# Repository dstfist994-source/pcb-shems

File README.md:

# Industrial IoT Smart Edge Device & Isolated Energy Controller

**A robust, mixed-signal hardware platform designed for AC mains energy monitoring, power conversion, and isolated load control. Engineered with high-voltage clearance, discrete signal shifting, and inductive load protection.**

---

## 📖 Overview

This **Smart Edge Node** is an industrial/home energy monitoring and switching board that bridges high-voltage AC mains power with low-voltage microcontroller logic. Designed with a focus on **analog hardware reliability**, **power distribution**, and **galvanic isolation**, the design integrates on-board AC-DC regulated conversion, discrete MOSFET level translation, and an optoisolated transistor relay driver with flyback suppression.

The system utilizes an **ESP8266 (Lolin)** for edge processing and software-driven UART communication with a **PZEM-004T** metering module, enabling real-time telemetry publication over Wi-Fi (MQTT/HTTP) while safely controlling heavy AC electrical loads.

---

## 📸 Visuals

| **3D PCB Render** | **PCB Layout & Routing** | **Hardware Schematic** |
|:---:|:---:|:---:|
|  |  |  |
| *KiCad 3D Ray-traced Board View* | *2-Layer Trace & High-Voltage Clearance* | *System Schematic Architecture* |

---

## ⚡ Hardware & Analog Engineering Highlights

### 1. Power Management & Bulk Decoupling
* **Integrated AC-DC Conversion:** Employs an on-board **Hi-Link HLK-5M05** module to convert $230\text{V AC}$ mains input directly down to a regulated $5\text{V DC}$ supply rail.
* **Transient Suppression & Ripple Filtering:** Features a high-capacity **$470\ \mu\text{F}$ bulk electrolytic capacitor ($C1$)** across the $5\text{V}$ rail to absorb voltage dips, suppress power supply ripple, and maintain rail stability during high instantaneous relay coil pull-in current.

### 2. Level Translation & Signal Integrity
* **Bi-Directional MOSFET Level Shifting:** Incorporates a discrete **BSS138 N-channel MOSFET Logic Level Converter ($U4$)** to bridge the $3.3\text{V CMOS}$ GPIO output of the ESP8266 ($D1$) to the $5\text{V TTL}$ driver logic without overdriving MCU input pins.
* **Isolated UART Interface:** Software Serial UART interface ($D6/D7$) connecting to the **PZEM-004T** energy metering frontend for accurate RMS Voltage, Current, Active Power, Frequency, and Power Factor acquisition.

### 3. Optoisolated Load Control & Inductive Suppression
* **Galvanic Isolation Drive Stage:** High-voltage AC switching is completely isolated from low-voltage digital control using a **PC817 Optocoupler** and an **S8050 NPN transistor** driver stage.
* **Back-EMF Inductive Protection:** A **1N4007 flyback suppression diode ($D1$)** is placed across the **SLA-05VDC** relay coil to clamp high-voltage inductive spikes generated during coil de-energization, protecting switching silicon from overshoot breakdown.
* **Visual Diagnostics:** Integrated LED indicator with current-limiting resistor ($1\text{ k}\Omega$) for visual relay status feedback.

### 4. High-Voltage PCB Layout & Safety Design
* **Creepage & Clearance:** Wide physical clearance and routing separation between the $230\text{V}$ AC mains region (Live/Neutral) and low-voltage $5\text{V}/3.3\text{V}$ DC signal planes to prevent electrical arcing.
* **Current-Handling Traces:** Heavy trace widths utilized on AC Live/Neutral routing and high-current relay switching paths to minimize trace impedance, drop, and thermal rise under heavy electrical load.

---

## 🛠 Subsystem Breakdown

| Subsystem | Circuitry / Components | Function |
| :--- | :--- | :--- |
| **Power Supply** | HLK-5M05 + $470\ \mu\text{F}$ Capacitor | AC-DC Step-down ($230\text{V AC} \to 5\text{V DC}$) & Rail Filtering |
| **Microcontroller** | ESP8266 (Lolin V3 Footprint) | Wireless Telemetry, MQTT, SoftSerial UART, GPIO Control |
| **Logic Level Conversion** | BSS138 MOSFET Level Shifter ($U4$) | $3.3\text{V} \leftrightarrow 5\text{V}$ Logic Level Translation |
| **Relay Driver** | PC817 Optocoupler + S8050 NPN + 1N4007 Diode | Isolated coil energization & Back-EMF suppression |
| **AC Load Control** | SLA-05VDC High-Power Relay | Heavy AC Load ON/OFF Disconnect |
| **Energy Measurement** | PZEM-004T AC Sensor | High-accuracy RMS Voltage, Current, & Power Telemetry |

---

## 👨‍💻 Authors

- **Suvam Seth**
  *Power Engineering Student | PCB Design | Analog Electronics & Systems Design*

- **Sarin Sanyal**
  *Power Engineering Student | Analog & Mixed-Signal Circuit Design | Embedded Hardware | AI*

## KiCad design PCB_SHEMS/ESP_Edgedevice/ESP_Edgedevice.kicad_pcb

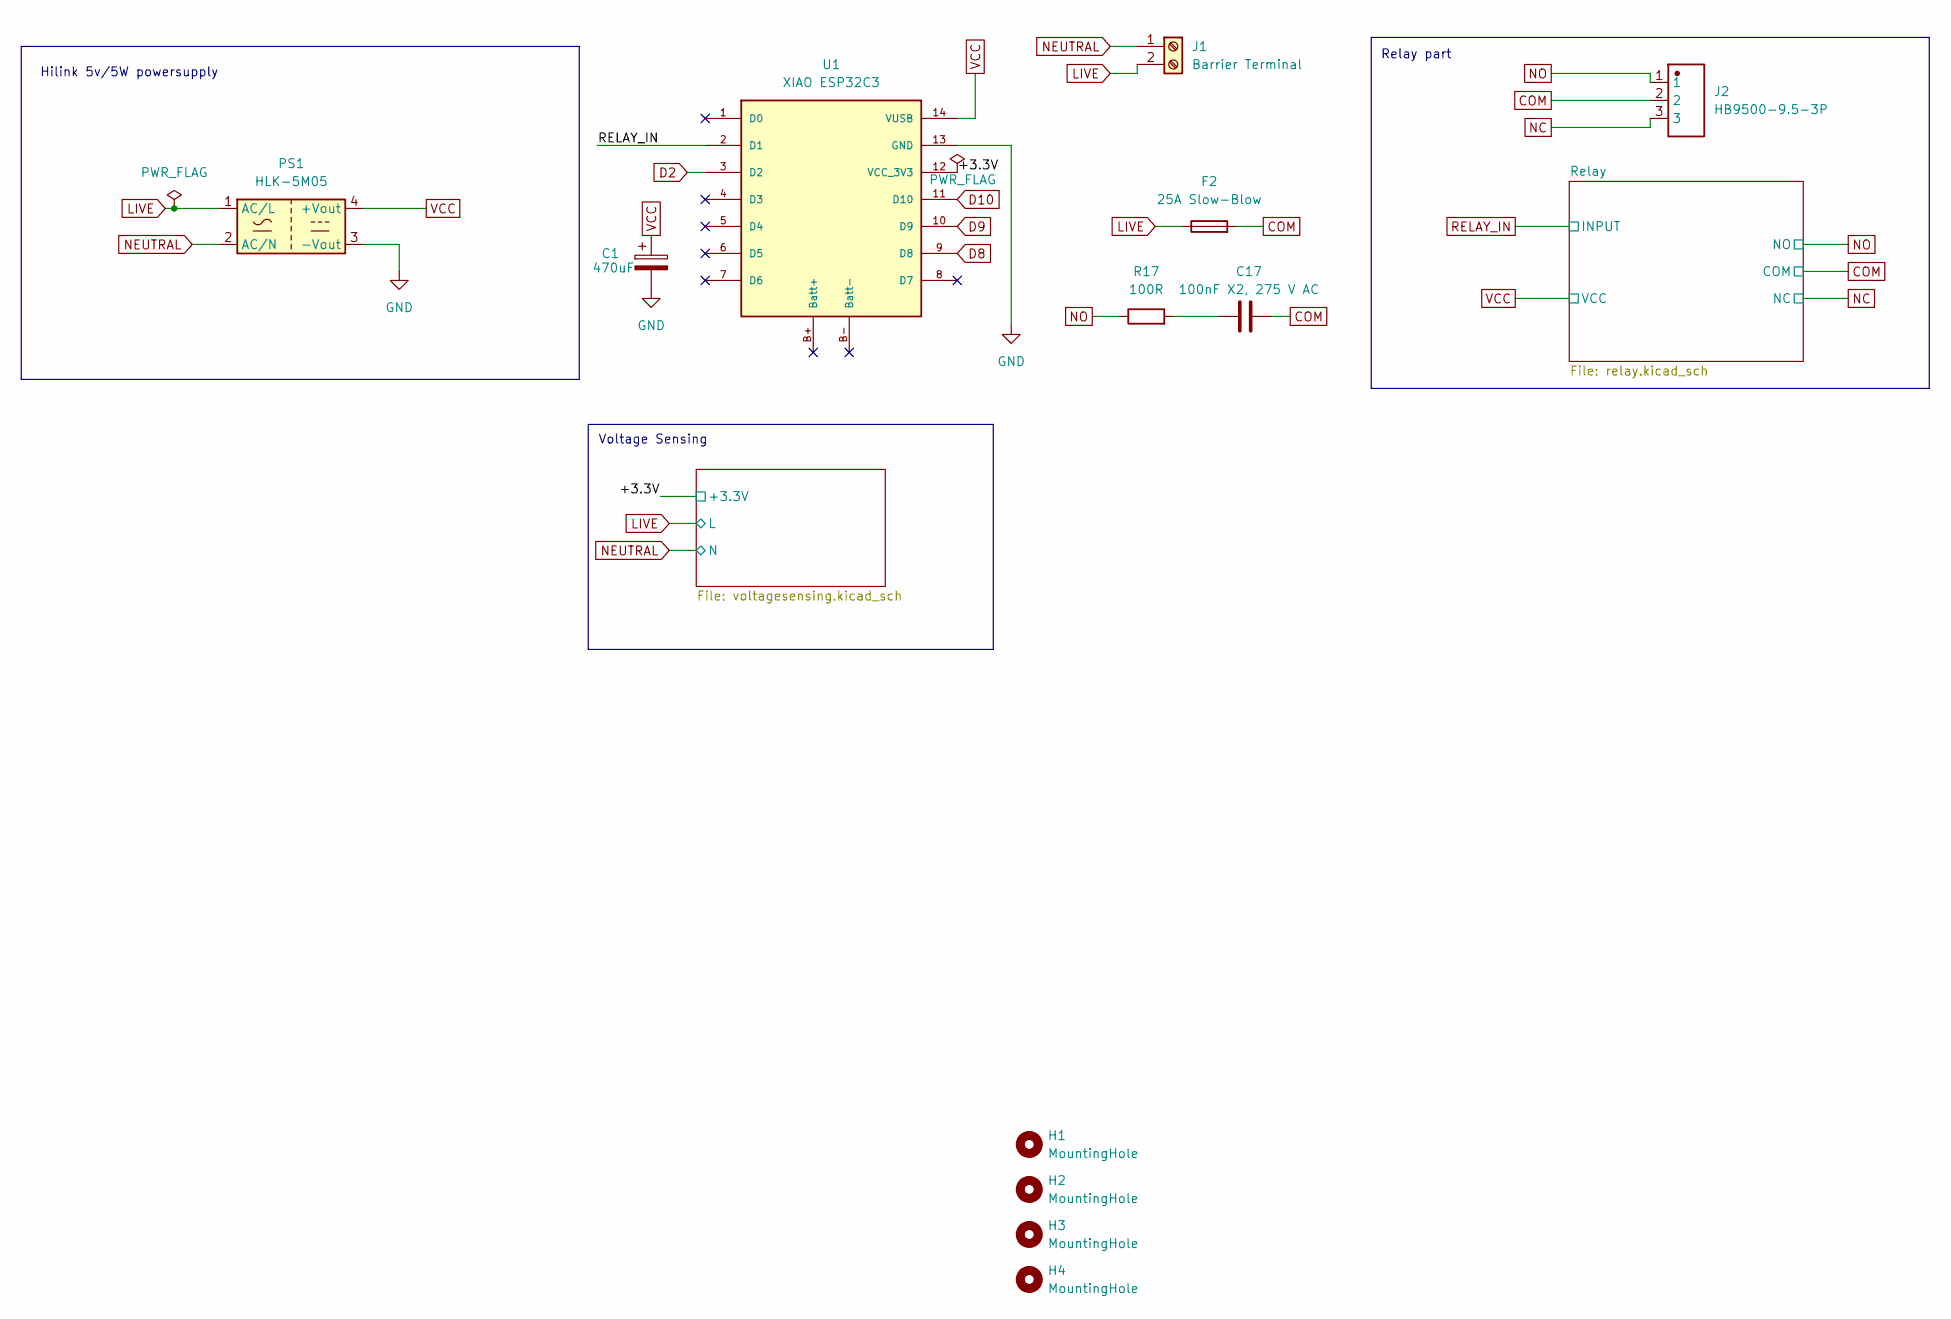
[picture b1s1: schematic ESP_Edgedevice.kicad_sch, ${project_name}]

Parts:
C1: 470uF; CP_Radial_D6.3mm_P2.50mm
C17: 100nF X2, 275 V AC; C_Rect_L18.0mm_W5.0mm_P15.00mm_FKS3_FKP3
F2: 25A Slow-Blow; Fuseholder_Cylinder-6.3x32mm_Schurter_0031-8002_Horizontal_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
H1, H2, H3, H4: MountingHole; MountingHole_2.1mm
J1: Barrier Terminal; PhoenixContact_MSTBA_2,5_2-G_1x02_P5.00mm_Horizontal
J2: HB9500-9.5-3P; HB9500_9.5-3P; Manufacturer Part HB9500-9.5-3P
PS1: HLK-5M05; Converter_ACDC_Hi-Link_HLK-5Mxx
R17: 100R; R_Axial_DIN0309_L9.0mm_D3.2mm_P12.70mm_Horizontal
U1: XIAO ESP32C3; XIAO_Socket_W15.24

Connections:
/+3.3V: U1.12 (VCC_3V3); also elsewhere on the board
COM: C17.2, F2.2, J2.2; also elsewhere on the board
D2: U1.3 (D2); also elsewhere on the board
D8: U1.9 (D8); also elsewhere on the board
D9: U1.10 (D9); also elsewhere on the board
D10: U1.11 (D10); also elsewhere on the board
GND: C1.2, PS1.3 (-Vout), U1.13 (GND); also elsewhere on the board
LIVE: F2.1, J1.2, PS1.1 (AC/L); also elsewhere on the board
NC: J2.3; also elsewhere on the board
NEUTRAL: J1.1, PS1.2 (AC/N); also elsewhere on the board
NO: J2.1, R17.1; also elsewhere on the board
unnamed: C17.1, R17.2
RELAY_IN: U1.2 (D1); also elsewhere on the board
VCC: C1.1, PS1.4 (+Vout), U1.14 (VUSB); also elsewhere on the board

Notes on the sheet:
Voltage Sensing
Relay part
Hilink 5v/5W powersupply

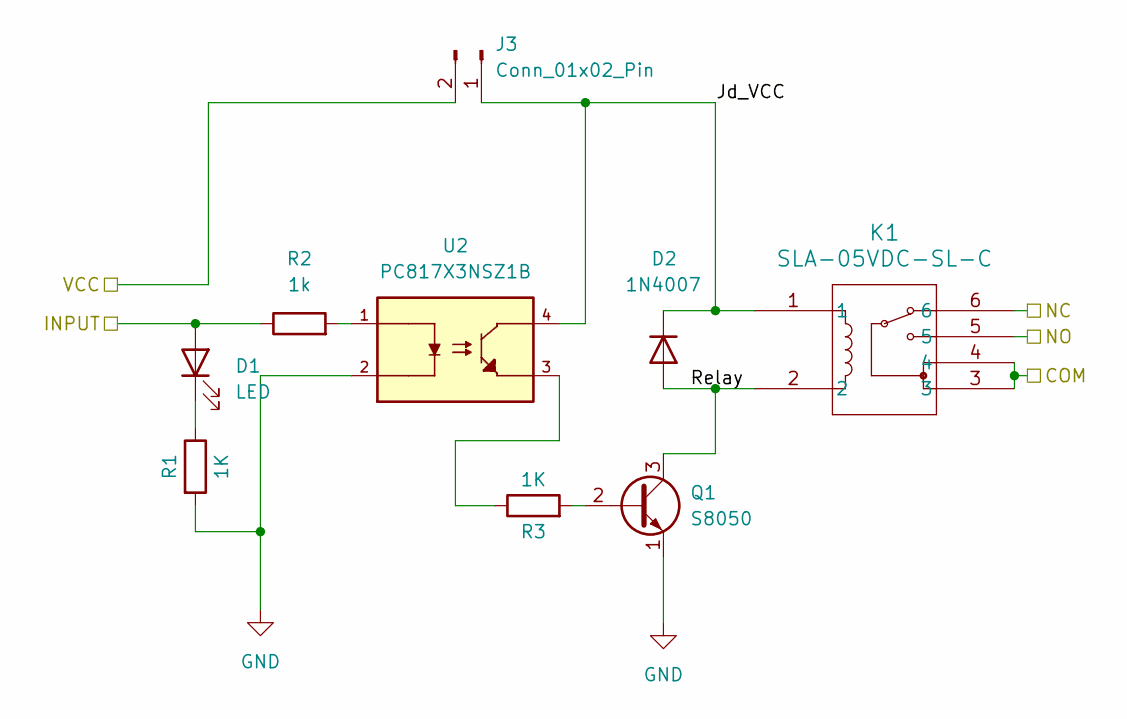
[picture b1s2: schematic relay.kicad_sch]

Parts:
D1: LED; LED_D3.0mm
D2: 1N4007; D_DO-41_SOD81_P10.16mm_Horizontal
J3: Conn_01x02_Pin; PinHeader_1x02_P2.54mm_Vertical
K1: SLA-05VDC-SL-C; RELAY-TH_SLA-XXVDC-XX-C
Q1: S8050; TO-92_Inline_Wide
R1, R3: 1K; R_1206_3216Metric
R2: 1k; R_1206_3216Metric
U2: PC817X3NSZ1B; DIP-4_W7.62mm; PARTREV October 7, 2016

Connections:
/Relay/Jd_VCC: D2.1 (K), J3.1, K1.1, U2.4
/Relay/Relay: D2.2 (A), K1.2, Q1.3 (C)
COM: K1.3, K1.4; also elsewhere on the board
GND: Q1.1 (E), R1.2, U2.2; also elsewhere on the board
NC: K1.6; also elsewhere on the board
NO: K1.5; also elsewhere on the board
unnamed: D1.1 (K), R1.1
unnamed: Q1.2 (B), R3.2
unnamed: R2.2, U2.1
unnamed: R3.1, U2.3
RELAY_IN: D1.2 (A), R2.1; also elsewhere on the board
VCC: J3.2; also elsewhere on the board

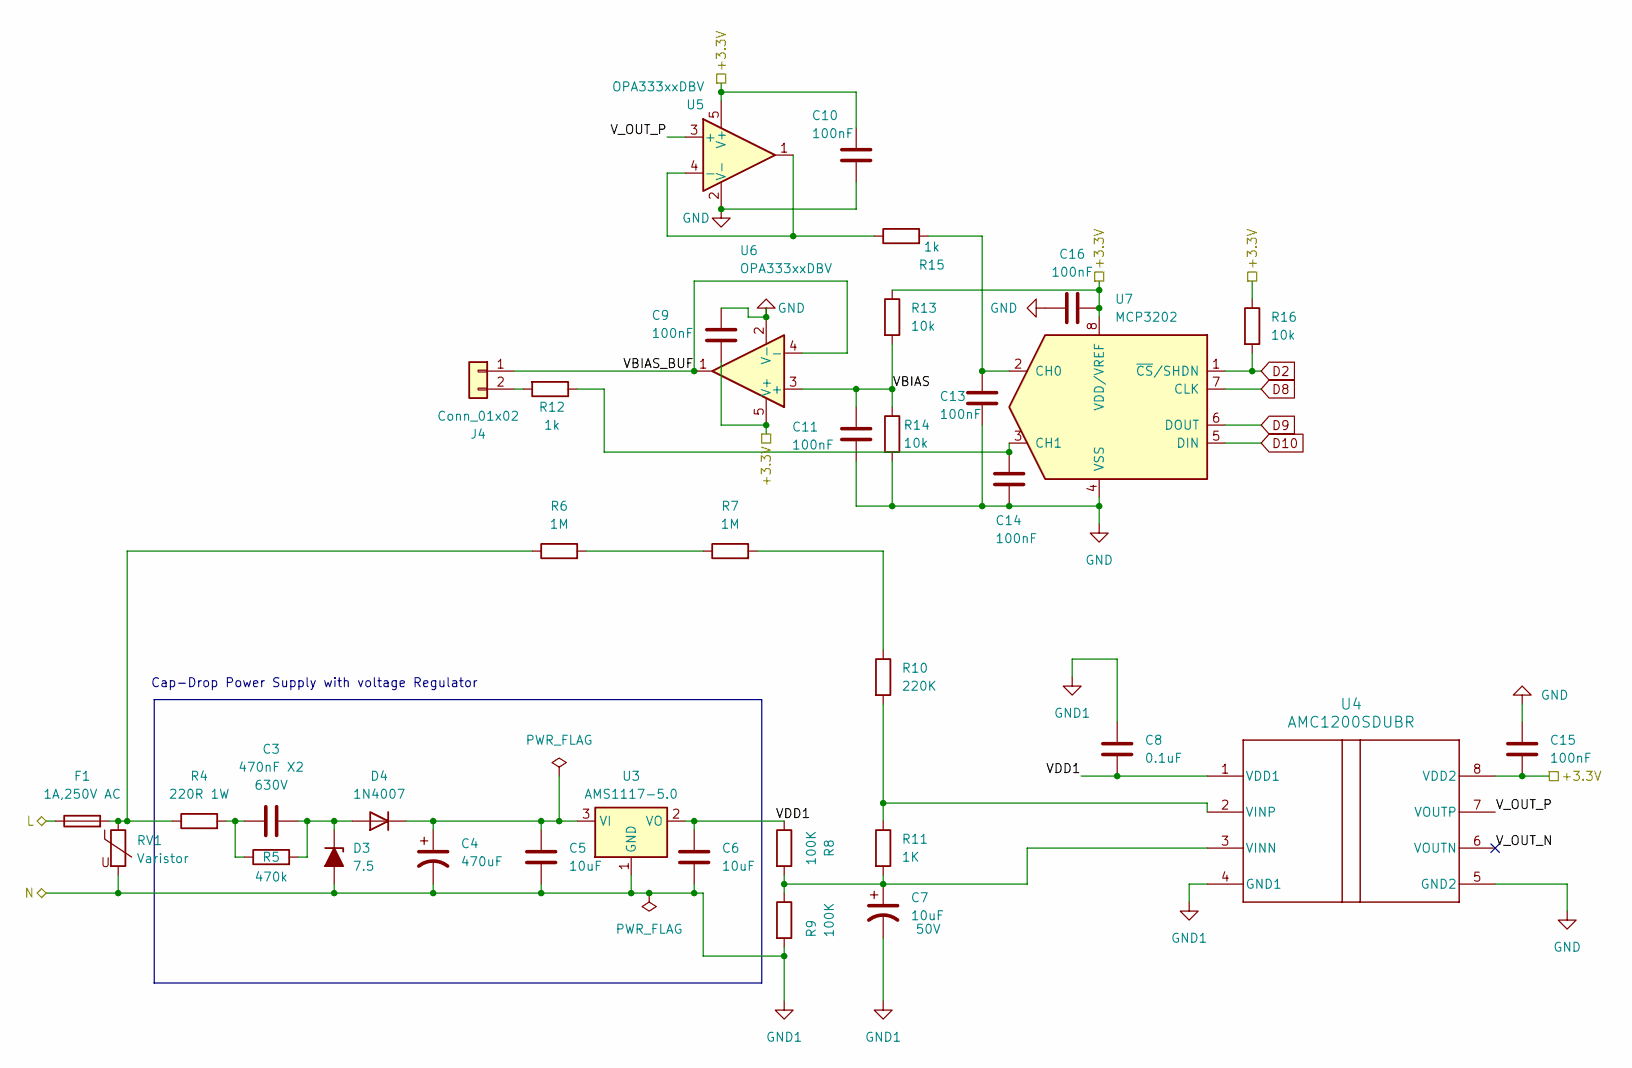
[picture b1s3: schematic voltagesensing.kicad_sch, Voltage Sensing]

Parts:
C3: 470nF X2; C_Rect_L26.5mm_W8.5mm_P22.50mm_MKS4; voltage 630V
C4: 470uF; CP_Radial_D10.0mm_P5.00mm
C5: 10uF; C_1206_3216Metric
C6: 10uF; CP_Radial_D5.0mm_P2.50mm
C7: 10uF; CP_Radial_D5.0mm_P2.50mm; Voltage 50V
C8: 0.1uF; C_1206_3216Metric
C9, C10, C11, C13, C14, C15, C16: 100nF; C_1206_3216Metric
D3: 7.5; D_MiniMELF
D4: 1N4007; D_DO-41_SOD81_P10.16mm_Horizontal
F1: 1A,250V AC; Fuseholder_Cylinder-5x20mm_Schurter_0031_8201_Horizontal_Op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
J4: Conn_01x02; PinHeader_1x02_P2.54mm_Vertical
R4: 220R 1W; R_Axial_DIN0414_L11.9mm_D4.5mm_P15.24mm_Horizontal
R5: 470k; R_Axial_DIN0207_L6.3mm_D2.5mm_P10.16mm_Horizontal
R6, R7: 1M; R_Axial_DIN0207_L6.3mm_D2.5mm_P10.16mm_Horizontal
R8, R9: 100K; R_1206_3216Metric
R10: 220K; R_1206_3216Metric
R11: 1K; R_1206_3216Metric
R12, R15: 1k; R_1206_3216Metric
R13, R14, R16: 10k; R_1206_3216Metric
RV1: Varistor; RV_Disc_D12mm_W4.2mm_P7.5mm
U3: AMS1117-5.0; SOT-223-3_TabPin2
U4: AMC1200SDUBR; DUB0008A-IPC_A
U5, U6: OPA333xxDBV; SOT-23-5
U7: MCP3202; TSSOP-8_4.4x3mm_P0.65mm

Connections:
/+3.3V: C9.1, C10.2, C15.2, C16.1, R13.1, R16.1, U4.8 (VDD2), U5.5 (V+), U6.5 (V+), U7.8 (VDD/VREF); also elsewhere on the board
/voltagesensing.kicad_sch/VBIAS: C11.1, R13.2, R14.1, U6.3 (+)
/voltagesensing.kicad_sch/VBIAS_BUF: J4.1, U6.1, U6.4 (-)
/voltagesensing.kicad_sch/VDD1: C6.1, C8.2, R8.1, U3.2 (VO), U4.1 (VDD1)
/voltagesensing.kicad_sch/V_OUT_N: U4.6 (VOUTN)
/voltagesensing.kicad_sch/V_OUT_P: U4.7 (VOUTP), U5.3 (+)
D2: R16.2, U7.1 (~CS/SHDN); also elsewhere on the board
D8: U7.7 (CLK); also elsewhere on the board
D9: U7.6 (DOUT); also elsewhere on the board
D10: U7.5 (DIN); also elsewhere on the board
GND: C9.2, C10.1, C11.2, C13.2, C14.2, C15.1, C16.2, R14.2, U4.5 (GND2), U5.2 (V-), U6.2 (V-), U7.4 (VSS); also elsewhere on the board
LIVE: F1.1; also elsewhere on the board
NEUTRAL: C4.2, C5.2, C6.2, C7.2, C8.1, D3.2 (A), R9.2, RV1.2, U3.1 (GND), U4.4 (GND1); also elsewhere on the board
unnamed: C3.1, R4.2, R5.1
unnamed: C3.2, D3.1 (K), D4.2 (A), R5.2
unnamed: C4.1, C5.1, D4.1 (K), U3.3 (VI)
unnamed: F1.2, R4.1, R6.1, RV1.1
unnamed: J4.2, R12.2
unnamed: R6.2, R7.1
unnamed: R7.2, R10.1
unnamed: C7.1, R8.2, R9.1, R11.2, U4.3 (VINN)
unnamed: R10.2, R11.1, U4.2 (VINP)
unnamed: R15.1, U5.1, U5.4 (-)
unnamed: C13.1, R15.2, U7.2 (CH0)
unnamed: C14.1, R12.1, U7.3 (CH1)

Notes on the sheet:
Cap-Drop Power Supply with voltage Regulator

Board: 2 copper layers, 57 parts (0 on the bottom side), 36 nets, no tracks yet.

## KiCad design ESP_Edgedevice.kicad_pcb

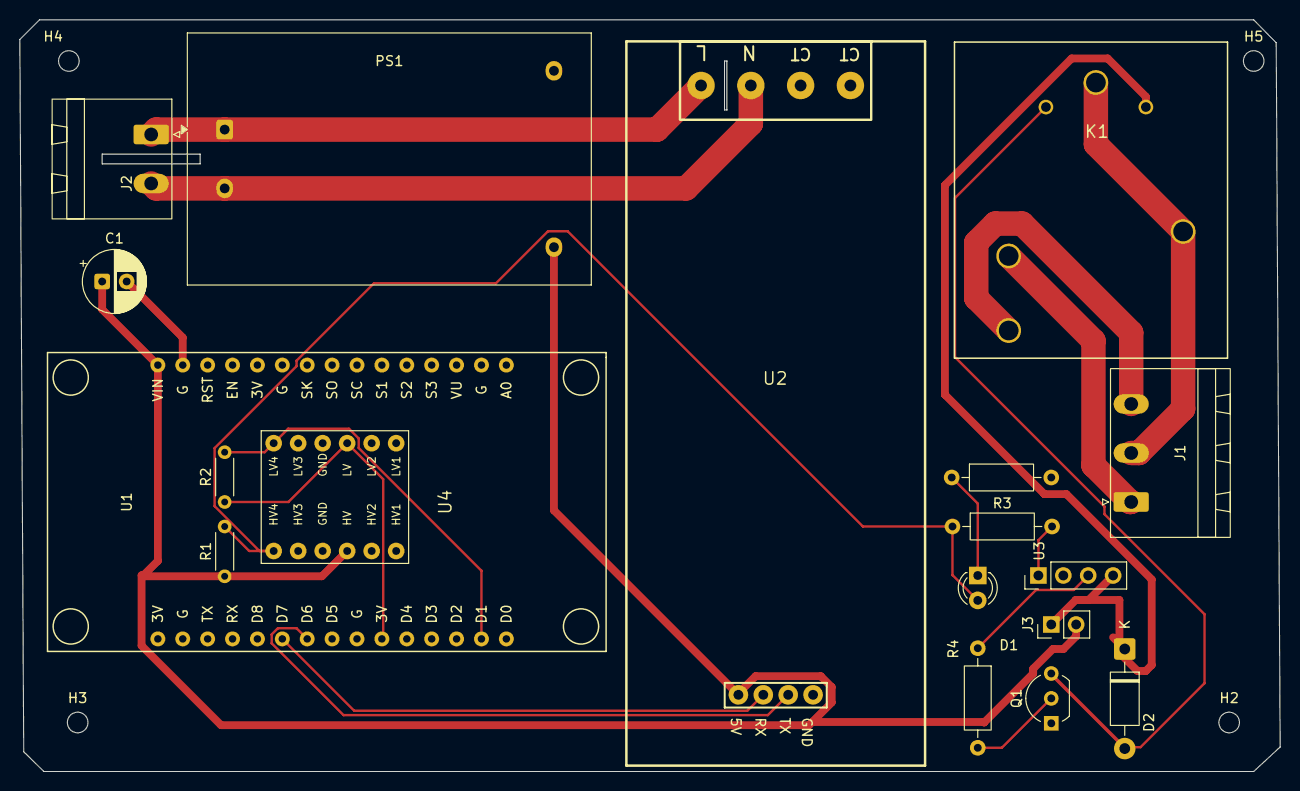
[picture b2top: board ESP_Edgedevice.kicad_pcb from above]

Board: 2 copper layers, 128.6 x 76.7 mm, 22 parts (0 on the bottom side), 18 nets.

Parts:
C1: 470uF; CP_Radial_D6.3mm_P2.50mm
D1: LED; LED_D3.0mm
D2: 1N4007; D_DO-41_SOD81_P10.16mm_Horizontal
H2, H3, H4, H5: MountingHole; MountingHole_2.1mm
J1: HB9500-9.5-3P; PhoenixContact_MSTBA_2,5_3-G_1x03_P5.00mm_Horizontal
J2: Barrier Terminal; PhoenixContact_MSTBA_2,5_2-G_1x02_P5.00mm_Horizontal
J3: Conn_01x02_Pin; PinHeader_1x02_P2.54mm_Vertical
K1: SLA-05VDC-SL-C; K_SLA_C_NFR
PS1: HLK-5M05; Converter_ACDC_Hi-Link_HLK-5Mxx
Q1: S8050; TO-92_Inline_Wide
R1, R2: 10k; R_Axial_DIN0204_L3.6mm_D1.6mm_P5.08mm_Horizontal
R3: 2.2K; R_Axial_DIN0207_L6.3mm_D2.5mm_P10.16mm_Horizontal
R4, R13: 1K; R_Axial_DIN0207_L6.3mm_D2.5mm_P10.16mm_Horizontal
U1: ESP8266_Lolin; NodeMCU-LoLinV3
U2: PZEM-004T; PZEM-004T_V3
U3: PC817X3NSZ1B; PinHeader_1x04_P2.54mm_Vertical
U4: LLC_BSS138

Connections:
+3.3V: R2.1, U1.21 (3V), U4.8 (LV)
/D1: R2.2, U1.17 (D1), U4.1 (LV4)
/D6: U1.24 (D6), U2.2 (TX)
/D7: U1.25 (D7), U2.3 (RX)
/Relay/Jd_VCC: D2.1 (K), J3.1, K1.1, U3.4
/Relay/Relay: D2.2 (A), K1.2, Q1.3 (C)
COM: J1.2, K1.3, K1.4
GND: C1.2, PS1.3 (-Vout), Q1.1 (E), R13.2, U1.14 (G), U2.1 (GND), U3.2, U4.5 (GND), U4.6 (GND)
LIVE: J2.2, PS1.1 (AC/L), U2.8 (AC-L)
NC: J1.3, K1.6
NEUTRAL: J2.1, PS1.2 (AC/N), U2.7 (AC-N)
NO: J1.1, K1.5
unnamed: D1.1 (K), R13.1
unnamed: Q1.2 (B), R4.2
unnamed: R3.2, U3.1
unnamed: R4.1, U3.3
RELAY_IN: D1.2 (A), R1.2, R3.1, U4.2 (HV4)
VCC: C1.1, J3.2, PS1.4 (+Vout), R1.1, U1.15 (VIN), U2.4 (VCC), U4.7 (HV)
